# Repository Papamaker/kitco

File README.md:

# La console Kitco

Auteur: François Jacob

Ceci est le projet de la console Kitco. Le but de ce projet est de fournir un kit de console portable pour un coût réduit en matériel.

Rendez-vous sur www.kitco.fr

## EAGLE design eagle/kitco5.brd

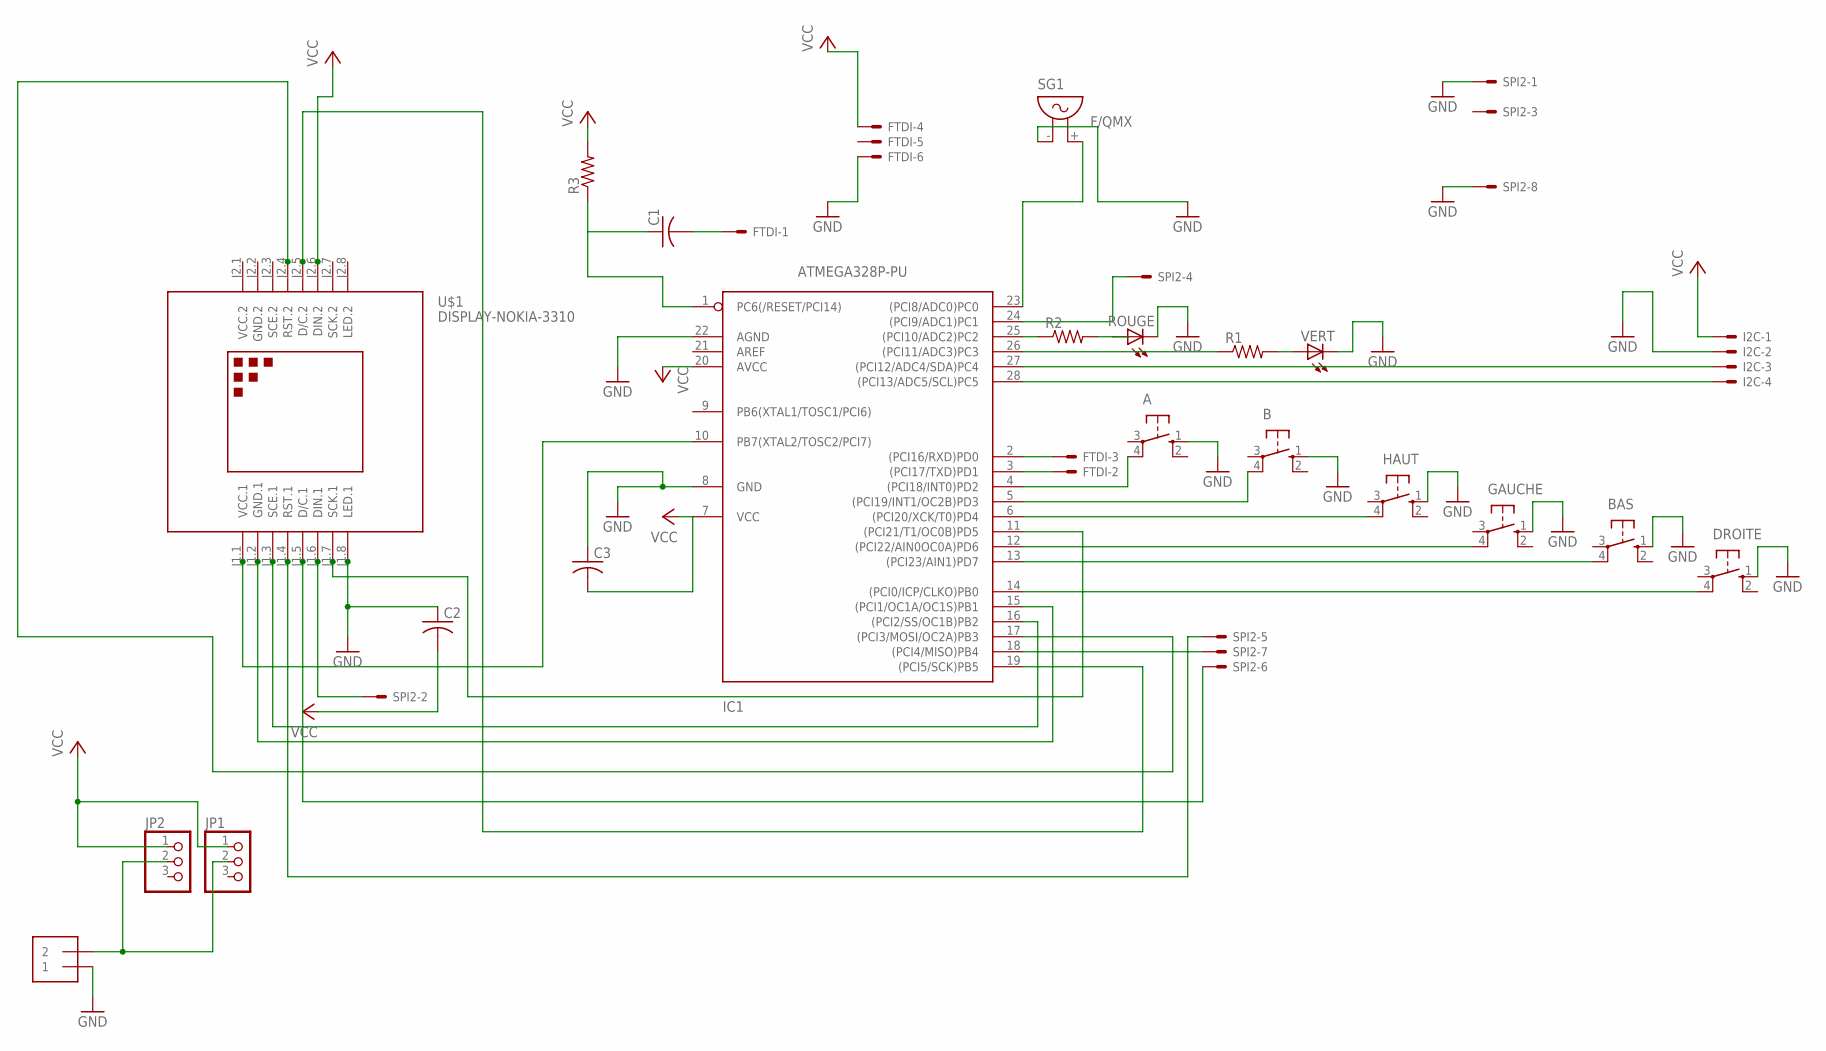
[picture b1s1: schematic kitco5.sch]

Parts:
A: 10-XX; B3F-10XX
B: 10-XX; B3F-10XX
BAS: 10-XX; B3F-10XX
C1, C2, C3: C-US025-040X050; C025-040X050
DROITE: 10-XX; B3F-10XX
FTDI: 22-23-2061
GAUCHE: 10-XX; B3F-10XX
HAUT: 10-XX; B3F-10XX
I2C: 22-23-2041
IC1: ATMEGA328P-PU; DIL28-3
J1: 1X2-3.5MM
JP1, JP2: PINHD-1X3; 1X03
R1, R2, R3: R-US_0207/10; 0207/10
ROUGE: LED5MM
SG1: F/QMX
SPI2: 22-23-2081
U$1: DISPLAY-NOKIA-3310
VERT: LED5MM

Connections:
GND: A.1 (S), B.1 (S), BAS.1 (S), C2.1, C3.1, DROITE.1 (S), FTDI.6, GAUCHE.1 (S), HAUT.1 (S), I2C.2, IC1.8 (GND), IC1.22 (AGND), J1.1, ROUGE.K (C), SG1.- (1), SPI2.1, SPI2.8, U$1.J1.8 (LED.1), VERT.K (C)
GND.2: U$1.J2.2 (GND.2)
unnamed: A.4 (P1), IC1.4 ((PCI18/INT0)PD2)
unnamed: B.4 (P1), IC1.5 ((PCI19/INT1/OC2B)PD3)
unnamed: IC1.11 ((PCI21/T1/OC0B)PD5), U$1.J1.7 (SCK.1)
unnamed: GAUCHE.4 (P1), IC1.12 ((PCI22/AIN0OC0A)PD6)
unnamed: BAS.4 (P1), IC1.13 ((PCI23/AIN1)PD7)
unnamed: DROITE.4 (P1), IC1.14 ((PCI0/ICP/CLKO)PB0)
unnamed: I2C.3, IC1.27 ((PCI12/ADC4/SDA)PC4)
unnamed: I2C.4, IC1.28 ((PCI13/ADC5/SCL)PC5)
unnamed: J1.2, JP1.2, JP2.2
unnamed: HAUT.4 (P1), IC1.6 ((PCI20/XCK/T0)PD4)
unnamed: FTDI.2, IC1.3 ((PCI17/TXD)PD1)
unnamed: IC1.26 ((PCI11/ADC3)PC3), R1.1
unnamed: R1.2, VERT.A
unnamed: IC1.25 ((PCI10/ADC2)PC2), R2.1
unnamed: R2.2, ROUGE.A
unnamed: IC1.24 ((PCI9/ADC1)PC1), SPI2.4
unnamed: IC1.17 ((PCI3/MOSI/OC2A)PB3), U$1.J2.4 (RST.2)
unnamed: IC1.19 ((PCI5/SCK)PB5), U$1.J2.5 (D/C.2)
unnamed: IC1.15 ((PCI1/OC1A/OC1S)PB1), U$1.J1.2 (GND.1)
unnamed: IC1.16 ((PCI2/SS/OC1B)PB2), U$1.J1.3 (SCE.1)
unnamed: FTDI.3, IC1.2 ((PCI16/RXD)PD0)
unnamed: IC1.18 ((PCI4/MISO)PB4), SPI2.7
unnamed: IC1.23 ((PCI8/ADC0)PC0), SG1.+ (2)
unnamed: SPI2.5, U$1.J1.4 (RST.1)
unnamed: C1.2, FTDI.1
unnamed: SPI2.6, U$1.J1.5 (D/C.1)
unnamed: SPI2.2, U$1.J1.6 (DIN.1)
unnamed: C1.1, IC1.1 (PC6(/RESET/PCI14)), R3.1
unnamed: IC1.10 (PB7(XTAL2/TOSC2/PCI7)), U$1.J1.1 (VCC.1)
VCC: C2.2, C3.2, FTDI.4, I2C.1, IC1.7 (VCC), IC1.20 (AVCC), JP1.1, JP2.1, R3.2, U$1.J2.6 (DIN.2)
VCC.2: U$1.J2.1 (VCC.2)

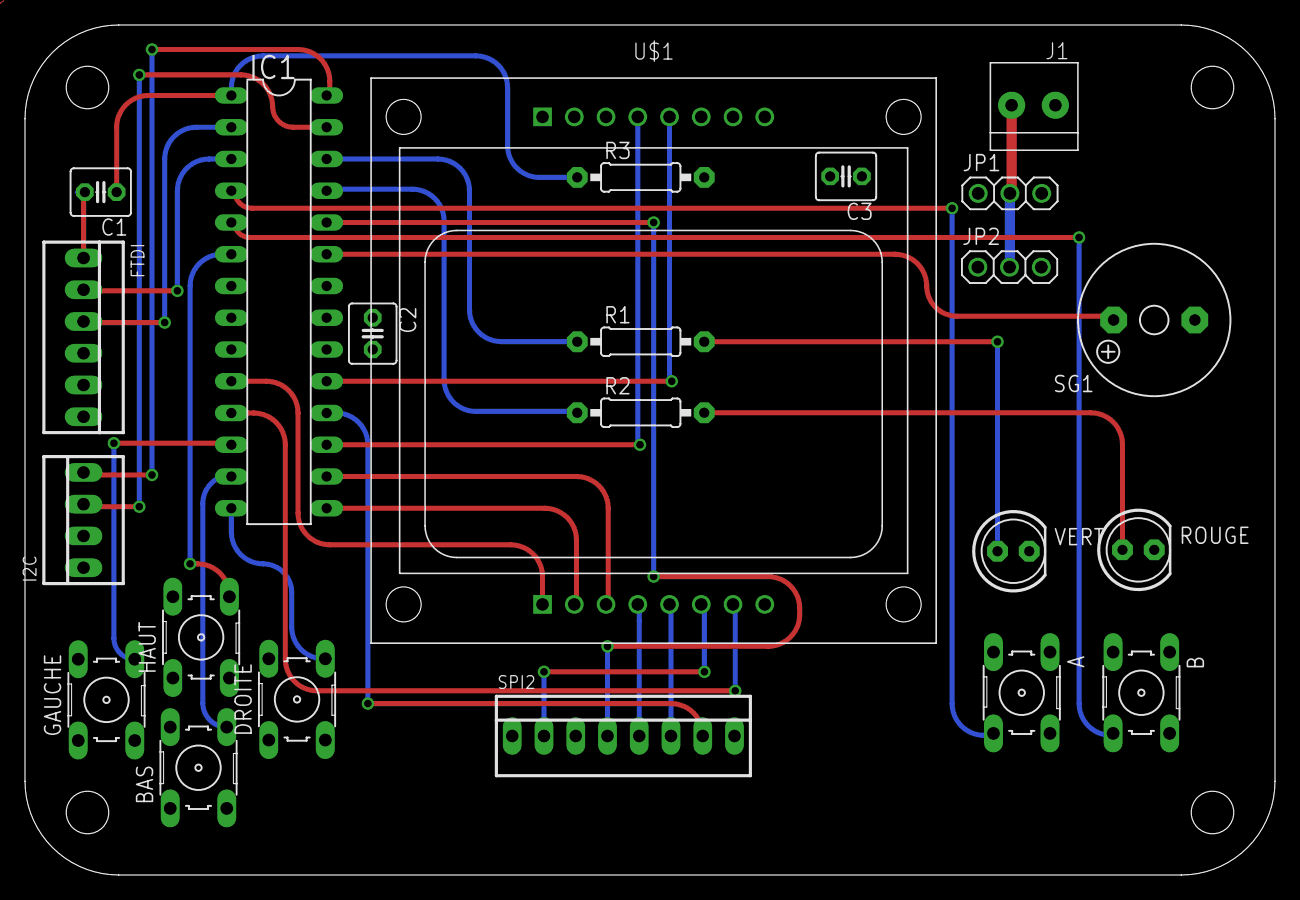
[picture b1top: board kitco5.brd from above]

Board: 2 copper layers, 100.0 x 68.0 mm, 23 parts (0 on the bottom side), 31 nets.

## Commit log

2016-03-24 :lollipop: Added .gitattributes & .gitignore files
2016-03-25 mise en place de l'arborescence
    mise en place des répertoire et du premier prog de démo de la
    présentation makerfaire paris à l'école 42
2016-03-28 commit avant de déplacer les fichiers
    commit de l’appli pacrob en cours de dev (je vais la déplacer en local
    chez moi)
2016-03-28 travail du weekend pascal
    sur l’appli pac-rob
2016-03-28 remplacement par le raccourci
    raccourci supprimé à tort restauré
2016-04-10 amélioration pacrob
    plusieurs niveaux + sprites pour commandes
2016-04-20 nouveau proto 0.2
    Ajout du proto 0.2
2016-04-24 Added files via upload
    V1 du jeu de snake
2016-04-24 Added files via upload
2016-04-24 ficher déplacé au bon endroit
    déplacement du fichier au bon endroit
2016-04-24 motifs mineurs dans snake
    - ajout de initBoard(1) à appeler dans le setup
    -ajout de litboutons() pour update valeurs touches
    - motif du randomseed
    - ajout de nourriture tout le temps
    - haut et bas inversé…
    - ajout de son et LED rouge quand perdu
2016-04-26 amélioration IDE + touches + niveaux en plus
2016-05-16 nouveau jeu Breakout pour démo programmez
2016-05-23 Fichiers gerber
    Fichiers gerber proto 0.2
2016-09-11 choses non comptées
2016-09-11 ajout bootloader
    première version: téléversement et chargement de CFG.HEX depuis le
    bootloader: OK
2016-09-12 Rename gamebuino_boot.c to boot.c
2016-09-12 Rename boot.c to kitcoboot.c
2016-09-14 travail en cours bootloader et compagnie
2016-10-01 travail pour porter les différents jeux sur la kitsch v1
2016-10-02 nouvelle arborescence
    beaucoup plus clean
2016-10-02 clean boot loader directory
2016-10-02 effacer ancienne arborescence
2016-11-03 Rename kitcop4.sch to eagle/kitcop4.sch
2016-11-03 Rename kitcop4.brd to eagle/kitcop4.brd
2017-01-08 ajout de pong et tetris et mac librairie
2017-01-08 renommage répertoire 1.0 en zip pour ne pas avoir le num de version dans le nom du cep
2017-01-22 ajout fichier pour tutoriel Sokoban
    Ajout jeu sokoban
2017-01-22 pb avec schéma
2017-01-22 commit sans motif
2017-01-22 bug de synchro
2017-01-22 Revert "bug de synchro"
    This reverts commit 3db693749081f5e34a9b1ed0ed48bc87a60fd485.
2017-01-22 Revert "commit sans motif"
    This reverts commit a898fcdef14e03ab11d1c6ade1f6804252e3e49f.
2017-01-22 ré-ajout schéma suite à bug
2017-01-22 ajout de l'étape 2 du codage de Sokoban
2017-01-25 sokoban3
    ajout de la troisième étape du tutoriel sokoban
2017-01-31 prise en compte remarques sokoban1
2017-02-27 Add files via upload
    This is an other version of the kitco case that I've made.
2017-05-20 proof of concept pour utiliser snap (scratch plus évolué) avec kitco
2018-01-15 Create spaceinvaders
2018-01-15 Create toto
2018-01-15 Rename invaders.ino to spaceinvaders.ino
2018-01-25 Rename kitco.hex to tetrisBootloader.hex
2018-05-18 Create zanzibar21.ino
    commit initial

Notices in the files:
parts and their libraries:
diy-modules: Released under the Creative Commons Attribution 4.0 International License: http://creativecommons.org/licenses/by/4.0
